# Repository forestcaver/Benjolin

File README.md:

# Benjolin

CC-By-NC 4.0, 2019

SMT Benjolin. Strictly for non-commercial use.

- - - -

This is a SMT version of the Benjolin with some modifications to power supply and protection.

Built and verified, Oct 2019

Rob Hordijk (the designer of the Benjolin) has kindly given permission Oct 27, 2019) for this to be shared on GitHub with the proviso that these files cannot be used by third parties for commercial use.

If you make changes and want to republish, please contact Rob before doing so!

- - - -

- - - -

## v1.0 ##

Files: Eagle pcb board, Eagle pcb schematic, Gerber files for the pcb, Eagle panel board, Gerber files for the panel (I use one-sided aluminium pcb with no copper), 2x images of the finished module

I used a combination of Kweiwen's schematic on his github as well as the electro-music schematics. I then added the power supply and protection.

The main issue (which is an original feature) for me is that the output volume is quite low. This is true of the original design. You can adjust one of the resistors just before the filter to boost the gain. But this can cause subtle distortion in the filter. A better way is to add a gain cell at the output (see v1.6)

- - - -

## v1.6 ##

This version adds an opamp to add gain to the output to approx 10v p-p. It also normalises T1 to osc 2 cv input
(can still be attenuated with the pot), normalises T2 to osc 1 cv and T2 to filter cv input.

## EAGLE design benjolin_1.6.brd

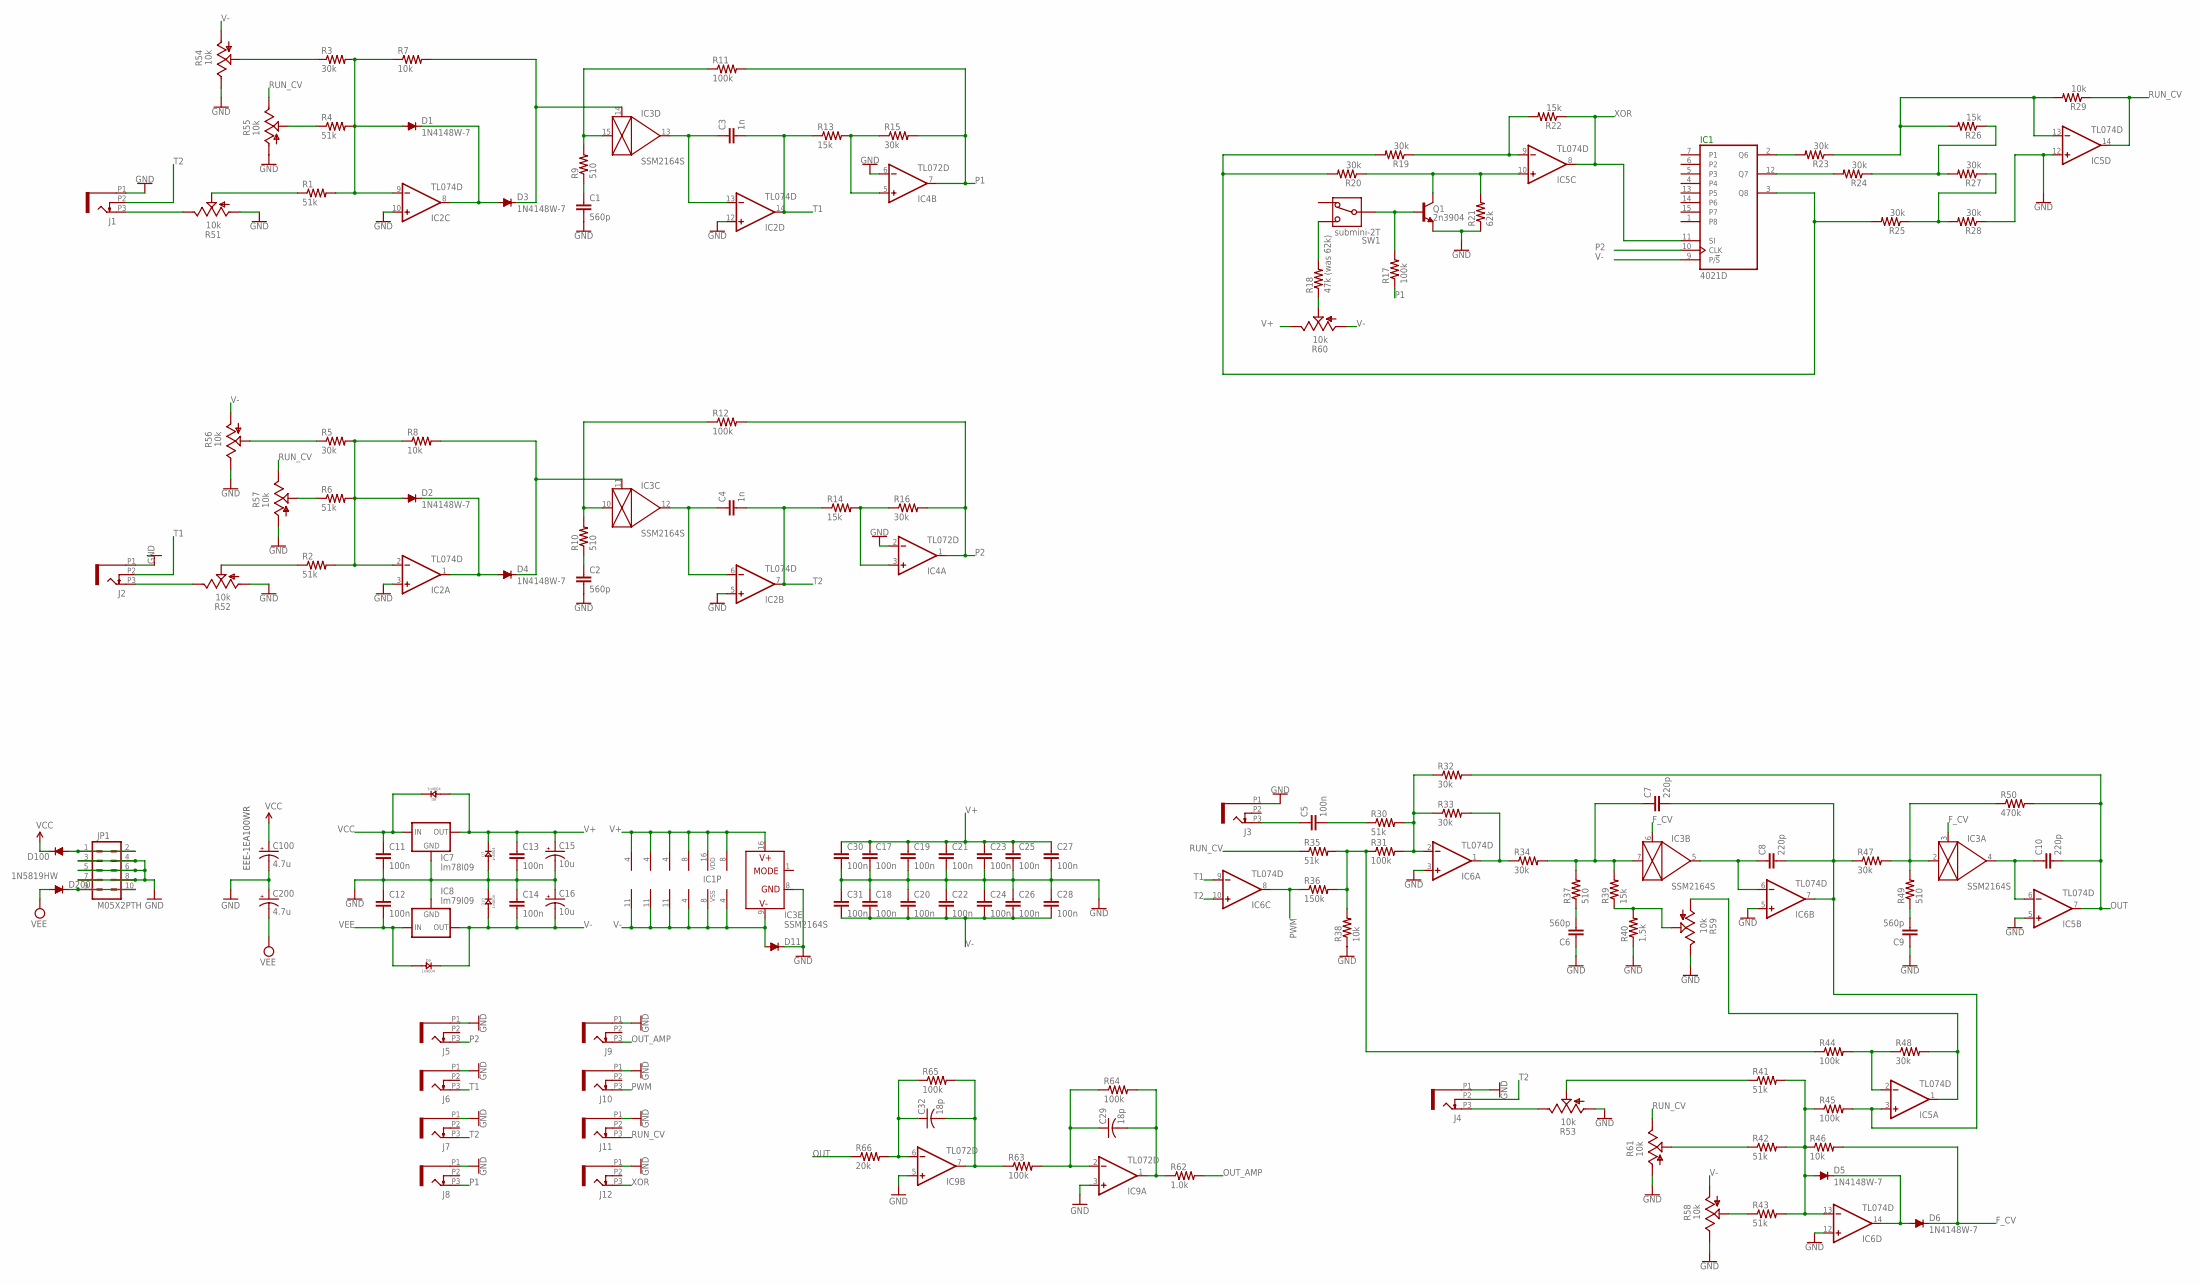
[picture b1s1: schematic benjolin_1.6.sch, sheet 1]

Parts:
C1, C2, C6, C9: 560p; C0603
C3, C4: 1n; C0603
C5, C11, C12, C13, C14, C17, C18, C19, C20, C21, C22, C23, C24, C25, C26, C27, C28, C30, C31: 100n; C0603
C7, C8, C10: 220p; C0603
C15, C16: 10u; PANASONIC_A
C29, C32: 18p; C0603
C100, C200: 4.7u; PANASONIC_A
D1, D2, D3, D4, D5, D6: 1N4148W-7; SOD123
D7, D8, D9, D10: 1n4004; DO-214AC
D11, D100, D200: 1N5819HW; SOD123
IC1: 4021D; SO16
IC2, IC5, IC6: TL074D; SO14
IC3: SSM2164S; SOIC16N
IC4, IC9: TL072D; SO08
IC7: lm78l09; 78LXX
IC8: lm79l09; 79LXX
J1, J2, J3, J4, J5, J6, J7, J8, J9, J10, J11, J12: PJ301_THONKICONN6; WQP_PJ_301M6
JP1: M05X2PTH; AVR_ICSP
Q1: 2n3904; SOT23-3
R1, R2, R4, R6, R30, R35, R41, R42, R43: 51k; R0603
R3, R5, R15, R16, R19, R20, R23, R24, R25, R27, R28, R32, R33, R34, R47, R48: 30k; R0603
R7, R8, R29, R38, R46: 10k; R0603
R9, R10, R37, R49: 510; R0603
R11, R12, R17, R31, R44, R45, R63, R64, R65: 100k; R0603
R13, R14, R22, R26, R39: 15k; R0603
R18: 47k (was 62k); R0603
R21: 62k; R0603
R36: 150k; R0603
R40: 1.5k; R0603
R50: 470k; R0603
R51, R52, R53: 10k; ALPS_POT_NARROW
R54, R55, R56, R57, R58, R59, R60, R61: 10k; ALPS_POT_VERTICAL_PS
R62: 1.0k; R0603
R66: 20k; R0603
SW1: submini-2T; SPDT-SUB

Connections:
F_CV: D6.C, IC3.3 (CTRL), IC3.6 (CTRL), R46.2
GND: C1.2, C2.2, C6.1, C9.1, C11.2, C12.1, C13.2, C14.1, C15.-, C16.+, C17.2, C18.1, C19.2, C20.1, C21.2, C22.1, C23.2, C24.1, C25.2, C26.1, C27.2, C28.1, C30.2, C31.1, C100.-, C200.+, D7.1 (+), D10.2 (-), D11.C, IC2.3 (+IN), IC2.5 (+IN), IC2.10 (+IN), IC2.12 (+IN), IC3.8 (GND), IC4.2 (-IN), IC4.6 (-IN), IC5.5 (+IN), IC5.12 (+IN), IC6.3 (+IN), IC6.5 (+IN), IC6.12 (+IN), IC7.GND, IC8.GND, IC9.3 (+IN), IC9.5 (+IN), J1.P1 (1), J2.P1 (1), J3.P1 (1), J4.P1 (1), J5.P1 (1), J6.P1 (1), J7.P1 (1), J8.P1 (1), J9.P1 (1), J10.P1 (1), J11.P1 (1), J12.P1 (1), JP1.3, JP1.4, JP1.5, JP1.6, JP1.7, JP1.8, Q1.2 (E), R21.1, R28.1, R38.1, R40.1, R51.P$3 (A), R52.P$3 (A), R53.P$3 (A), R54.P$1 (E), R55.P$3 (A), R56.P$1 (E), R57.P$3 (A), R58.P$1 (E), R59.P$1 (E), R61.P$3 (A)
unnamed: J1.P3 (3), R51.P$1 (E)
unnamed: J2.P3 (3), R52.P$1 (E)
unnamed: R1.1, R51.P$2 (S)
unnamed: R2.1, R52.P$2 (S)
unnamed: D1.A, IC2.9 (-IN), R1.2, R3.2, R4.2, R7.1
unnamed: D100.A, JP1.1, JP1.2
unnamed: D2.A, IC2.2 (-IN), R2.2, R5.2, R6.2, R8.1
unnamed: R6.1, R57.P$2 (S)
unnamed: R5.1, R56.P$2 (S)
unnamed: R3.1, R54.P$2 (S)
unnamed: R4.1, R55.P$2 (S)
unnamed: D1.C, D3.A, IC2.8 (OUT)
unnamed: D4.C, IC3.11 (CTRL), R8.2
unnamed: D2.C, D4.A, IC2.1 (OUT)
unnamed: D3.C, IC3.14 (CTRL), R7.2
unnamed: R43.1, R58.P$2 (S)
unnamed: C29.2, IC9.1 (OUT), R62.1, R64.2
unnamed: C2.1, R10.1
unnamed: IC3.10 (IN), R10.2, R12.1
unnamed: D200.C, JP1.9, JP1.10
unnamed: IC3.15 (IN), R9.2, R11.1
unnamed: C1.1, R9.1
unnamed: C4.1, IC2.6 (-IN), IC3.12 (OUT)
unnamed: C3.1, IC2.13 (-IN), IC3.13 (OUT)
unnamed: IC4.3 (+IN), R14.2, R16.1
unnamed: IC4.5 (+IN), R13.2, R15.1
unnamed: R18.2, SW1.P$1
unnamed: R18.1, R60.P$2 (S)
unnamed: Q1.1 (B), R17.2, SW1.P$2
unnamed: IC5.10 (+IN), Q1.3 (C), R20.1, R21.2
unnamed: IC5.9 (-IN), R19.1, R22.2
unnamed: IC1.2 (Q6), R23.2
unnamed: IC1.12 (Q7), R24.2
unnamed: IC1.3 (Q8), R19.2, R20.2, R25.2
unnamed: R24.1, R26.1, R27.2
unnamed: R25.1, R27.1, R28.2
unnamed: IC5.13 (-IN), R23.1, R26.2, R29.2
unnamed: R31.1, R35.2, R36.2, R38.2, R44.1
unnamed: C5.1, J3.P3 (3)
unnamed: C5.2, R30.1
unnamed: IC6.2 (-IN), R30.2, R31.2, R32.1, R33.1
unnamed: IC6.1 (OUT), R33.2, R34.1
unnamed: IC5.2 (-IN), R44.2, R48.1
unnamed: R39.1, R40.2, R59.P$2 (S)
unnamed: C6.2, R37.1
unnamed: C7.1, IC3.7 (IN), R34.2, R37.2, R39.2
unnamed: C8.1, IC3.5 (OUT), IC6.6 (-IN)
unnamed: C7.2, C8.2, IC5.3 (+IN), IC6.7 (OUT), R45.2, R47.1
unnamed: D5.A, IC6.13 (-IN), R41.2, R42.2, R43.2, R45.1, R46.1
unnamed: C9.2, R49.1
unnamed: IC3.2 (IN), R47.2, R49.2, R50.1
unnamed: C10.1, IC3.4 (OUT), IC5.6 (-IN)
unnamed: IC5.1 (OUT), R48.2, R59.P$3 (A)
unnamed: D5.C, D6.A, IC6.14 (OUT)
unnamed: R42.1, R61.P$2 (S)
unnamed: J4.P3 (3), R53.P$1 (E)
unnamed: R41.1, R53.P$2 (S)
unnamed: C32.1, IC9.6 (-IN), R65.1, R66.2
unnamed: C29.1, IC9.2 (-IN), R63.2, R64.1
unnamed: C32.2, IC9.7 (OUT), R63.1, R65.2
OUT: C10.2, IC5.7 (OUT), R32.2, R50.2, R66.1
OUT_AMP: J9.P3 (3), R62.2
P1: IC4.7 (OUT), J8.P3 (3), R11.2, R15.2, R17.1
P2: IC1.10 (CLK), IC4.1 (OUT), J5.P3 (3), R12.2, R16.2
PWM: IC6.8 (OUT), J10.P3 (3), R36.1
RUN_CV: IC5.14 (OUT), J11.P3 (3), R29.1, R35.1, R55.P$1 (E), R57.P$1 (E), R61.P$1 (E)
T1: C3.2, IC2.14 (OUT), IC6.9 (-IN), J2.P2 (2), J6.P3 (3), R13.1
T2: C4.2, IC2.7 (OUT), IC6.10 (+IN), J1.P2 (2), J4.P2 (2), J7.P3 (3), R14.1
V+: C13.1, C15.+, C17.1, C19.1, C21.1, C23.1, C25.1, C27.1, C30.1, D7.2 (-), D8.1 (+), IC1.16 (VDD), IC2.4 (V+), IC3.16 (V+), IC4.8 (V+), IC5.4 (V+), IC6.4 (V+), IC7.OUT, IC9.8 (V+), R60.P$1 (E)
V-: C14.2, C16.-, C18.2, C20.2, C22.2, C24.2, C26.2, C28.2, C31.2, D9.2 (-), D10.1 (+), D11.A, IC1.8 (VSS), IC1.9 (P/!S), IC2.11 (V-), IC3.9 (V-), IC4.4 (V-), IC5.11 (V-), IC6.11 (V-), IC8.OUT, IC9.4 (V-), R54.P$3 (A), R56.P$3 (A), R58.P$3 (A), R60.P$3 (A)
VCC: C11.1, C100.+, D8.2 (-), D100.C, IC7.IN
VEE: C12.2, C200.-, D9.1 (+), D200.A, IC8.IN
XOR: IC1.11 (SI), IC5.8 (OUT), J12.P3 (3), R22.1

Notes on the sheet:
EEE-1EA100WR

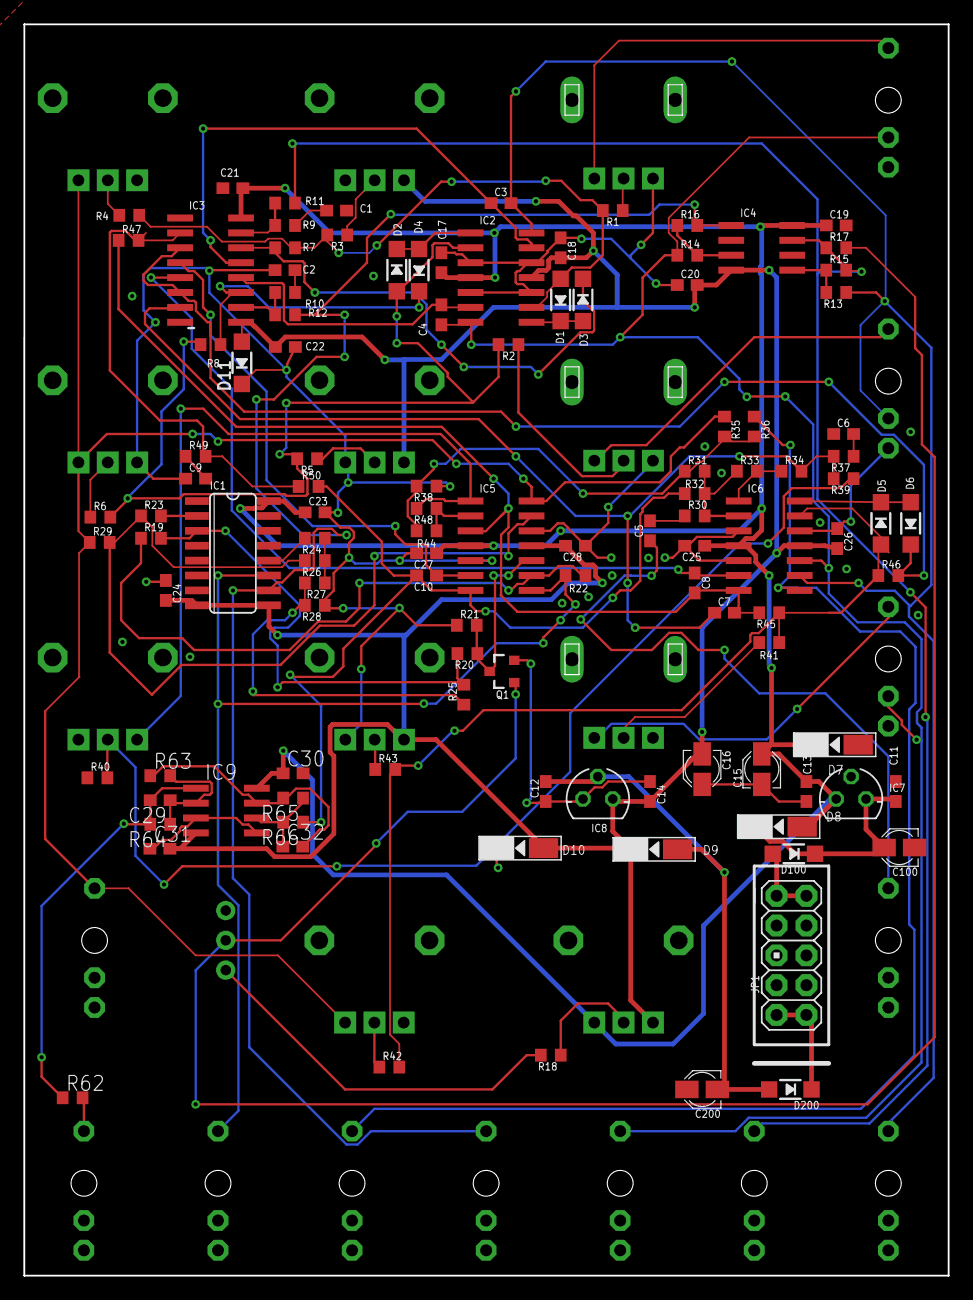
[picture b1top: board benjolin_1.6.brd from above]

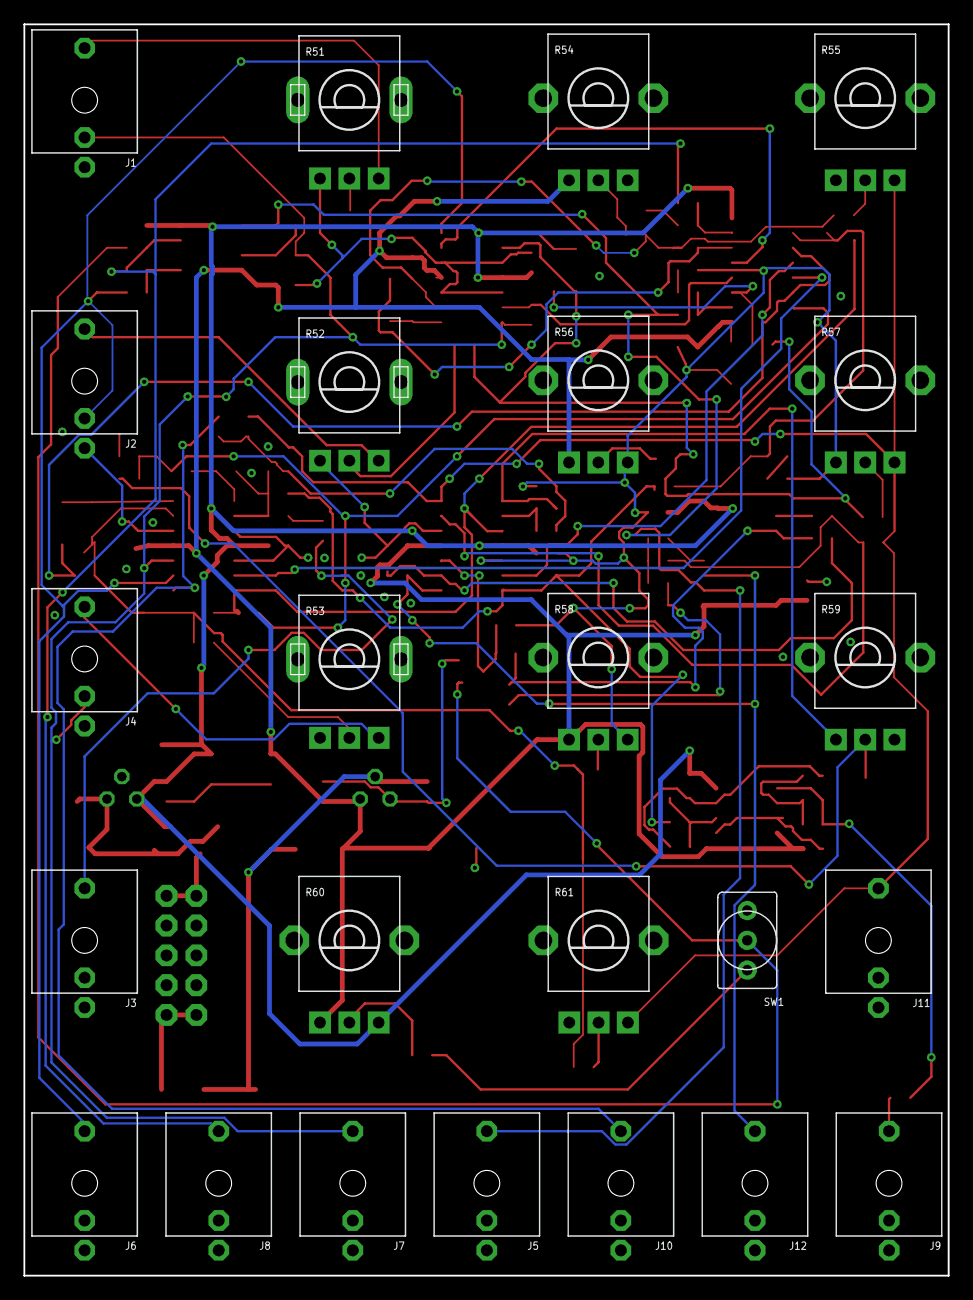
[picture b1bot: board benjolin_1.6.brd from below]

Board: 2 copper layers, 78.8 x 106.7 mm, 137 parts (24 on the bottom side), 75 nets.

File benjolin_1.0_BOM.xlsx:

benjolin_1.0_BOM
Qty | Value | Device | Package | Parts | Description | PROD_ID | VALUE
1 | 1.5k | R-US_R0603 | R0603 | R40 | RESISTOR, American symbol
6 | 100k | R-US_R0603 | R0603 | R11, R12, R17, R31, R44, R45 | RESISTOR, American symbol
17 | 100n | C-EUC0603 | C0603 | C5, C11, C12, C13, C14, C17, C18, C19, C20, C21, C22, C23, C24, C25, C26, C27, 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 | CAPACITOR, European symbol
3 | 10k | POT_USVERTICAL_NARROW | ALPS_POT_NARROW | R51, R52, R53
8 | 10k | POT_USVERTICAL_PS | ALPS_POT_VERTICAL_PS | R54, R55, R56, R57, R58, R59, R60, R61
5 | 10k | R-US_R0603 | R0603 | R7, R8, R29, R38, R46 | RESISTOR, American symbol
2 | 10u | CPOL-USA | PANASONIC_A | C15, C16 | POLARIZED CAPACITOR, American symbol
1 | 150k | R-US_R0603 | R0603 | R36 | RESISTOR, American symbol
5 | 15k | R-US_R0603 | R0603 | R13, R14, R22, R26, R39 | RESISTOR, American symbol
6 | 1N4148W-7 | 1N4148W-7 | SOD123 | D1, D2, D3, D4, D5, D6 | DIODE
3 | 1N5819HW | DIODE-SOD123 | SOD123 | D11, D100, D200 | DIODE
2 | 1n | C-EUC0603 | C0603 | C3, C4 | CAPACITOR, European symbol
4 | 1n4004 | D-SMA | DO-214AC | D7, D8, D9, D10 | DIODE
3 | 220p | C-EUC0603 | C0603 | C7, C8, C10 | CAPACITOR, European symbol
1 | 2n3904 | TRANS_NPN-MMBT2222AL | SOT23-3 | Q1 | NPN transistor | TRANS-08049 | 600mA/40V
16 | 30k | R-US_R0603 | R0603 | R3, R5, R15, R16, R19, R20, R23, R24, R25, R27, R28, R32, R33, R34, R47, R48 | RESISTOR, American symbol
2 | 4.7u | CPOL-USA | PANASONIC_A | C100, C200 | POLARIZED CAPACITOR, American symbol
1 | 4021D | 4021D | SO16 | IC1 | 8-bit static SHIFT REGISTER
1 | 470k | R-US_R0603 | R0603 | R50 | RESISTOR, American symbol
1 | 47k (was 62k) | R-US_R0603 | R0603 | R18 | RESISTOR, American symbol
4 | 510 | R-US_R0603 | R0603 | R9, R10, R37, R49 | RESISTOR, American symbol
9 | 51k | R-US_R0603 | R0603 | R1, R2, R4, R6, R30, R35, R41, R42, R43 | RESISTOR, American symbol
4 | 560p | C-EUC0603 | C0603 | C1, C2, C6, C9 | CAPACITOR, European symbol
1 | 62k | R-US_R0603 | R0603 | R21 | RESISTOR, American symbol
1 | M05X2PTH | M05X2PTH | AVR_ICSP | JP1 | Header 5x2
12 | PJ301_THONKICONN6 | PJ301_THONKICONN6 | WQP_PJ_301M6 | J1, J2, J3, J4, J5, J6, J7, J8, J9, J10, J11, J12
1 | SSM2164S | SSM2164S | SOIC16N | IC3
1 | TL072D | TL072D | SO08 | IC4 | OP AMP
3 | TL074D | TL074D | SO14 | IC2, IC5, IC6 | OP AMP
1 | lm78l09 | 78LXX | 78LXX | IC7 | VOLTAGE REGULATOR
1 | lm79l09 | 79LXX | 79LXX | IC8 | VOLTAGE REGULATOR
1 | submini-2T | SPDTT | SPDT-SUB | SW1 | SPDT Switch

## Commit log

2019-11-06 Add schematic pdf
2019-12-21 v1.6 - gain cell, normalisations
2020-02-14 Added BOMs

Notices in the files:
benjolin_1.6.sch:
Benjolin, layout by forestcaver, 2019. cc-by-nc-sa 4.0 2019
parts and their libraries:
SparkFun-DiscreteSemi: Licensing: Creative Commons ShareAlike 4.0 International - https://creativecommons.org/licenses/by-sa/4.0
